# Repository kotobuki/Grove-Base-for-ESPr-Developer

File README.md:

# Grove Base for ESPr Developer

A bridge between the [**Grove**](http://www.seeedstudio.com/wiki/Category:Grove) family by the Seeed Studio and [ESPr Developer](https://www.switch-science.com/catalog/2652/) by the Switch Science.

## Bill of Materials

|Part/Designator|Manufacture Part Number/Seeed SKU|Quantity|
|---------------|---------------------------------|--------|
|PCB||1|
|J1,J2,J3,J4|Seeed SKU: [320110033](http://www.seeedstudio.com/depot/index.php?main_page=opl_info&opl_id=4)|4|
|JP1|Digi-Key: [S9200-ND](http://www.digikey.com/product-search/en?keywords=952-1842-ND)|2|
|R1|Digi-Key: [P220KDBCT-ND](http://www.digikey.com/product-search/en?keywords=P220KDBCT-ND)|1|
|R2|Digi-Key: [P100KDBCT-ND](http://www.digikey.com/product-search/en?keywords=P100KDBCT-ND)|1|

## Compatible Grove Modules

* Sensors
  * [Grove - Button](http://www.seeedstudio.com/wiki/Grove_-_Button)
  * [Grove - Switch(P)](http://www.seeedstudio.com/wiki/Grove_-_Switch(P))
  * [Grove - Rotary Angle Sensor](http://www.seeedstudio.com/wiki/Grove_-_Rotary_Angle_Sensor)
  * [Grove - Slide Potentiometer](http://www.seeedstudio.com/wiki/Grove_-_Slide_Potentiometer)
  * [Grove - Touch Sensor](http://www.seeedstudio.com/wiki/Grove_-_Touch_Sensor)
  * [Grove - Light Sensor](http://www.seeedstudio.com/wiki/Grove_-_Light_Sensor)
  * [Grove - Single Axis Analog Gyro](http://www.seeedstudio.com/wiki/Grove_-_Single_Axis_Analog_Gyro)
  * [Grove - 3-Axis Digital Accelerometer (±16g)](http://www.seeedstudio.com/wiki/Grove_-_3-Axis_Digital_Accelerometer(%C2%B116g))
* Actuators
  * [Grove - LED Socket Kit](http://www.seeedstudio.com/wiki/Grove_-_LED)
  * [Grove - Buzzer](http://www.seeedstudio.com/wiki/Grove_-_Buzzer)
  * [Grove - Vibration Motor](http://www.seeedstudio.com/wiki/Grove_-_Vibration_Motor)
  * [Grove - Servo](http://www.seeedstudio.com/wiki/Grove_-_Servo)

## How to 'compile'?

Place an order at the [Fusion PCBA prototype](http://www.seeedstudio.com/service/index.php?r=pcb) service.

# License Information

This design document is licensed by Shigeru Kobayashi under the terms of the [Creative Commons Attribution-ShareAlike 4.0 International Public License](http://creativecommons.org/licenses/by-sa/4.0/).

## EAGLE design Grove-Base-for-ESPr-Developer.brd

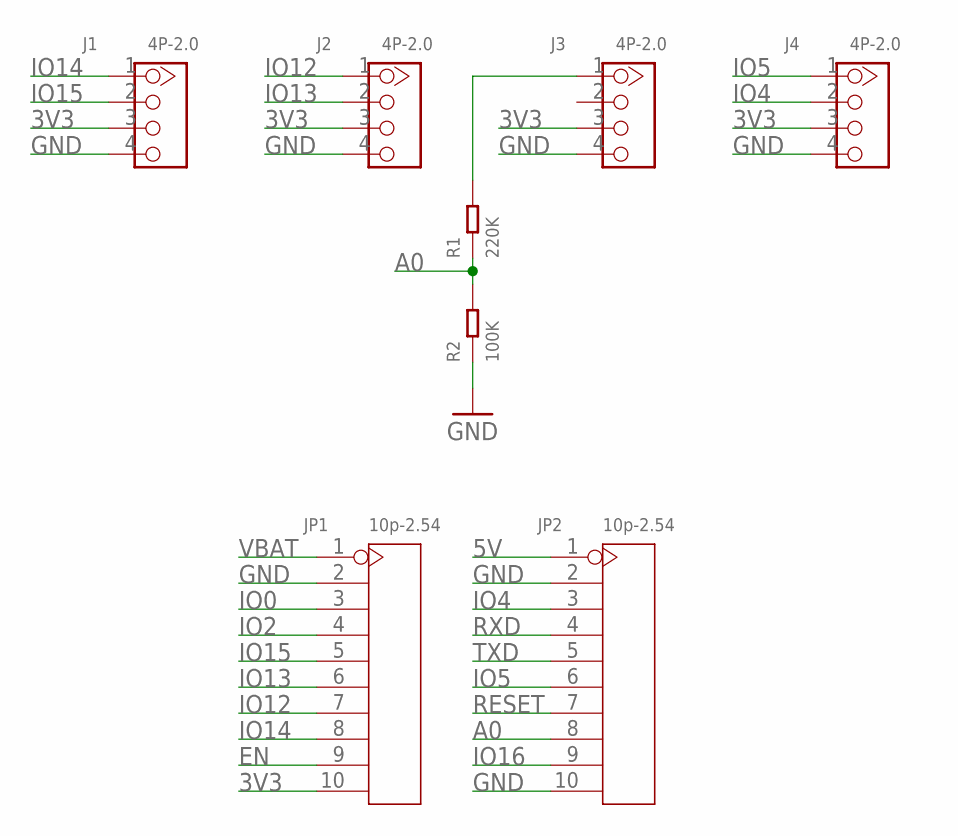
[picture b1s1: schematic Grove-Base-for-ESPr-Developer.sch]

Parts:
J1, J2, J3, J4: 4P-2.0; HW4-2.0
JP1, JP2: 10p-2.54; H10-2.54
R1: 220K; R0603
R2: 100K; R0603

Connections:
3V3: J1.3, J2.3, J3.3, J4.3, JP1.10
5V: JP2.1
A0: JP2.8, R1.1, R2.2
EN: JP1.9
GND: J1.4, J2.4, J3.4, J4.4, JP1.2, JP2.2, JP2.10, R2.1
IO0: JP1.3
IO2: JP1.4
IO4: J4.2, JP2.3
IO5: J4.1, JP2.6
IO12: J2.1, JP1.7
IO13: J2.2, JP1.6
IO14: J1.1, JP1.8
IO15: J1.2, JP1.5
IO16: JP2.9
unnamed: J3.1, R1.2
RESET: JP2.7
RXD: JP2.4
TXD: JP2.5
VBAT: JP1.1

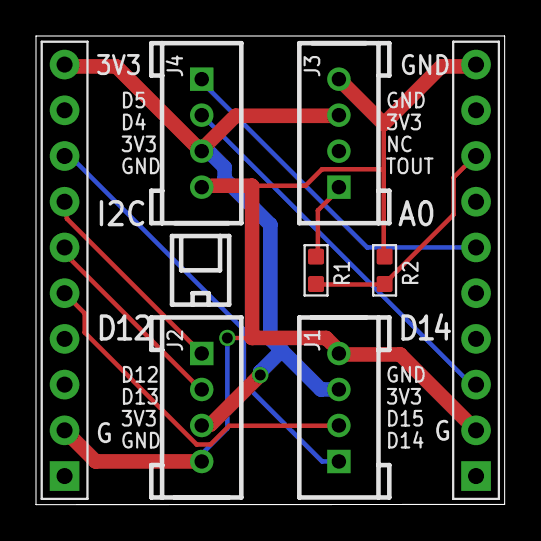
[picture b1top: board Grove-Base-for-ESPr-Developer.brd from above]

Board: 2 copper layers, 26.0 x 26.0 mm, 8 parts (0 on the bottom side), 10 nets.

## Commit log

2016-06-10 Update silk, BOM and README
    To fix issue #1 and missing components (R1 and R2) in the BOM
2016-06-14 Replace the IO14 pin of the IO14 connector with IO15
2016-06-20 Rotate 180 degree and revise labels
2016-07-31 Add compatible Grove modules
